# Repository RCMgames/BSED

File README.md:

# Byte Sized Encoder Decoder

Reads 8 quadrature encoders and communicates over I2C.

https://github.com/RCMgames/BSED

* Reads 8 quadrature encoders
* 1.0x0.85 inches, 25.4x21.59 millimeters
* I2C (Qwiic Compatible)
* powered by an ATmega328PB
* hand solderable surface mount components

### links 
(this repository contains an Arduino library, firmware for the board, and hardware for the board)
* [Documentation for Library](https://rcmgames.github.io/BSED/class_byte_sized_encoder_decoder.html)
* [Hardware](https://github.com/RCMgames/BSED/tree/main/extras/hardware)
  * If you buy PCBs from PCBWay through this link PCBWay generously gives me a 10% commission without costing you anything
    * https://www.pcbway.com/project/shareproject/ByteSizedEncoderDecoder_v1_1_a5a4bd50.html
* [Firmware](https://github.com/RCMgames/BSED/tree/main/extras/firmware)

### testing
Approximately 15000 encoder counts per second can be read from each encoder, but do your own testing before trusting this software.

See, and contribute to, this discussion on testing results: https://github.com/RCMgames/BSED/discussions/6

I've been working on [hardware and software for small wifi controlled robots](https://github.com/rcmgames) since 2020.

As I have designed increasingly small [circuit boards](https://github.com/rcmgames) for controlling servos and motors on robots, I started looking for a way to connect lots of quadrature encoders as inputs to a microcontroller. I was unable to find any existing Qwiic-compatible encoder reading boards that can handle multiple high-speed quadrature inputs. This board can help you control 8 motors with encoder feedback for precise control.

This version of firmware and library are compatible with version 1 of the hardware.

## Acknowledgements
* I would like to thank [PCBWay](https://www.pcbway.com/) for sponsoring prototyping runs of this project. PCBWay produces very nice boards, supports open source hardware, and gave me great support as I worked on this project. Special thanks to Liam!

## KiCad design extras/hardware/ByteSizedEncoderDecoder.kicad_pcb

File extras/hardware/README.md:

Here are the KiCAD and Gerber files for creating the circuit boards this firmware is designed to run on.

You could theoretically run it on a bare ATmega328 chip or another board, but the code is specialized for this board and uses hard-coded pin numbers.

### Bill Of Materials

* 1x assembled PCB
   * buy assembled PCBs from PCBWay with all the surface mount soldering done for you
      * https://www.pcbway.com/project/shareproject/ByteSizedEncoderDecoder_v1_1_a5a4bd50.html
   * or do your own surface mount soldering:
      * circuit board:
         * If you buy PCBs from PCBWay through this link PCBWay generously gives me a 10% commission without costing you anything
            * https://www.pcbway.com/project/shareproject/ByteSizedEncoderDecoder_v1_1_a5a4bd50.html
            * If you buy PCBs with another method (send ./PCB Production/gerbers-ByteSizedEncoderDecoder-v1.1.zip file) here's some info you might need: min track/spacing=6/6mil, min hole size=0.3mm
      * 2x JST SH https://www.digikey.com/en/products/detail/jst-sales-america-inc/SM04B-SRSS-TB/926710
      * 1x ATmega328PB TQFP https://www.digikey.com/en/products/detail/microchip-technology/ATMEGA328PB-AU/5638812
* 4x 1x08 0.1" female header pins

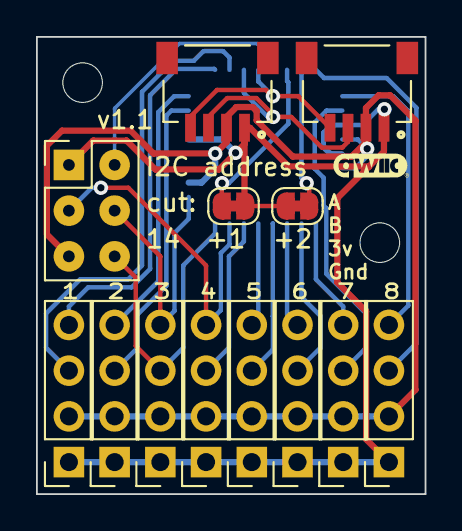
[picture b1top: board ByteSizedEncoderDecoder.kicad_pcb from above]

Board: 2 copper layers, 21.6 x 25.4 mm, 14 parts (1 on the bottom side), 23 nets.

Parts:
J1, J2: SM04B-SRSS-TB; JST_SM04B-SRSS-TB_LF__SN_
J3, J4, J5, J6, J7, J8, J9, J10: 1x4 female header pins 0.1"; PinSocket_1x04_P2.54mm_Vertical
J11: ICSP pads (for interfacing with pogo pins); PinHeader_2x03_P2.54mm_Vertical
NT1, NT2: NetTie_2; SolderJumper-2_P1.3mm_Bridged_RoundedPad1.0x1.5mm
U1: ATMEGA328PB, 32-TQFP; TQFP32_32A_MCH

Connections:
1a: J3.4, U1.25 (PC2(ADC2/PCINT10))
1b: J3.3, U1.26 (PC3(ADC3/PCINT11))
2a: J4.4, U1.24 (PC1(ADC1/PCINT9))
2b: J4.3, U1.23 (PC0(ADC0/PCINT8))
3a: J5.4, J11.4, U1.17 (PB5(SCK/PCINT5))
3b: J5.3, J11.6, U1.16 (PB4(PCINT4/MISO))
4a: J6.4, J11.3, U1.15 (PB3(PCINT3/OC2A/MOSI))
4b: J6.3, U1.14 (PB2(PCINT2/*SS/OC1B))
5a: J7.4, U1.13 (PB1(PCINT1/OC1A))
5b: J7.3, U1.12 (PB0(PCINT0/CLKO/ICP1))
6a: J8.4, U1.11 (PD7(PCINT23/AIN1))
6b: J8.3, U1.10 (PD6(PCINT22/OC0A/AIN0))
7a: J9.4, U1.9 (PD5(PCINT21/OC0B/T1))
7b: J9.3, U1.2 (PD4(PCINT20/XCK/T0))
8a: J10.4, U1.1 (PD3(PCINT19/OC2B/INT1))
8b: J10.3, U1.32 (PD2(INT0/PCINT18))
+3.3V: J1.2, J2.2, J3.2, J4.2, J5.2, J6.2, J7.2, J8.2, J9.2, J10.2, J11.5, U1.4 (VCC), U1.6 (VCC), U1.18 (AVCC)
GND: J1.1, J2.1, J3.1, J4.1, J5.1, J6.1, J7.1, J8.1, J9.1, J10.1, J11.1, NT1.2, NT2.2, U1.3 (GND), U1.5 (GND), U1.21 (GND)
unnamed: J11.2, U1.29 (PC6(*RESET/PCINT14))
unnamed: NT2.1, U1.30 (PD0(RXD/PCINT16))
unnamed: NT1.1, U1.31 (PD1(TXD/PCINT17))
scl: J1.4, J2.4, U1.28 (PC5(ADC5/SCL/PCINT13))
sda: J1.3, J2.3, U1.27 (PC4(ADC4/SDA/PCINT12))

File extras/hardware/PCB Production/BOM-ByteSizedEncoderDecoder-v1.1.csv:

"Reference","Value","Footprint","Datasheet","MPN","digikey link","Qty"
"J1, J2","SM04B-SRSS-TB","parts:JST_SM04B-SRSS-TB_LF__SN_","","SM04B-SRSS-TB","455-SM04B-SRSS-TBCT-ND","2"
"J3-J10","1x4 female header pins 0.1""","Connector_PinSocket_2.54mm:PinSocket_1x04_P2.54mm_Vertical","","do not place or purchase for PCB assembly","do not place or purchase for PCB assembly","8"
"J11","ICSP pads (for interfacing with pogo pins)","Connector_PinHeader_2.54mm:PinHeader_2x03_P2.54mm_Vertical","","DNP","n/a","1"
"NT1, NT2","NetTie_2","Jumper:SolderJumper-2_P1.3mm_Bridged_RoundedPad1.0x1.5mm","n/a","DNP","n/a","2"
"U1","ATMEGA328PB, 32-TQFP","parts:TQFP32_32A_MCH","https://ww1.microchip.com/downloads/en/DeviceDoc/40001907A.pdf","ATMEGA328PB-AU","ATMEGA328PB-AU-ND","1"

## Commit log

2024-04-29 Update LICENSE
2024-04-29 hardware
2024-04-29 v1.0
2024-04-30 add cad renders
2024-04-30 library in progress
2024-04-30 deploy: 8dd29d336e77dd8c4daba4778646e2d6889b8209
2024-04-30 update encoder-decoder
2024-04-30 deploy: 046cac742c8d4baad0db3d08612773206f1ff25a
2024-04-30 reorganize folder structure
2024-04-30 deploy: 2d5b23bad0e188f643c6baa7bf9b12540b59f16d
2024-04-30 deploy: 31a050b9553977e2c86f72bc61df8bde66f740fb
2024-04-30 deploy: 13ed9f9aa46e3a3bda3e58f608fc88605411b876
2024-04-30 deploy: ab928fcbb1b86652a8794f63fa460a9a4513bed8
2024-04-30 deploy: 84afdc5e6e0a747d372bb20c3929f94d8365258d
2024-04-30 deploy: c303ee2e10e87f0bf2600fd7d9f0ddd85b5686de
2024-04-30 deploy: 153a3cc4830325937b0cc74e23a72a057c9026b1
2024-04-30 deploy: 42606e44eb93d30457489d31a3c7e9c2847c78af
2024-04-30 update example
2024-04-30 deploy: 774eb56ce349130d670638287d715e6ee888093a
2024-05-07 update gitignore
2024-05-07 update platformio.ini for firmware
2024-05-07 update arduino-lint
2024-05-08 test board
2024-05-08 deploy: 01b0c1f6023ae4e33c418e61880ff35eee13345d
2024-05-08 v1.1.0
2024-05-08 deploy: 67b996aa6f6a97faa05906b41a075e949c9c572b
2024-05-08 deploy: 640480c00412bc1337e3585a3e5f8b7cb53df0ff
2024-05-08 deploy: bb7244fbd284bbc7ad47a52dc0187f68b3568ba5
2024-05-08 deploy: 7e8085068bbd8b13057818f64964c218992e2e56
2024-05-08 fix link
2024-05-08 deploy: a458f96f286acd965f08fd8f49f5cec25bdb48b6
2024-05-08 deploy: 14ca5f5b52133903bf38a4784cc1f2b9747e2a85
2024-05-08 bump version
2024-05-08 deploy: 7bbd7cdb57e76c38670929d11da173ca2910a05f
2024-05-09 deploy: 048ef7c90d99dd8eff31623957bd2c3ebbe873d6
2024-05-09 deploy: 2a934b6649cc7168c64c7b67ec340560d57a6b10
2024-05-09 deploy: a3604b6aac7eaefb1e5f3bccac8204a016fce239
2024-05-12 optimize
2024-05-12 deploy: fb2d7902788e27ff18d9947b4ad8f748b39b0092
2024-05-13 deploy: 2f7468403c3bd925679ba39fb191736a61d81592
2024-05-29 deploy: 74f35abdbd318b8f78ffbb224679e4cb3ca4ebe4
2024-05-29 deploy: 8e37769f0586e88a46bd28d0efe4ec72a4f9f8ab
2024-05-29 deploy: e4b2774a8f3d07a7a845fc5fdbfd15aabe313e3b
2024-06-01 v2 (velocity calculation and optimized communication)
2024-06-01 deploy: b679f1d842b0066368077c2ab96f58af3580ca96
2024-06-02 deploy: 839b353914f8db70047c15bcf3d98124fcc2ec9c
2024-06-02 deploy: 6aa68f8370d5924ac56f0b2442546248bb651869
2024-06-02 deploy: a9c9a5638a12d59224e219c59e79c5c87696c715
2024-06-02 add isvelnew
2024-06-02 deploy: 39d7633fdcdb4f595f88632ee2d85b5fb419ff88
2024-06-02 fix name conflict
2024-06-02 deploy: 23cef1622864e8e702abd88f5eae862d893afc08
2024-06-02 v2.1.2
2024-06-02 reset velocity when resetting position
2024-06-02 deploy: e5274b7ba16d88198c7ac8ed3aa3f12359599ac6
2024-06-02 v2.2.2
2024-06-02 deploy: e7d1fd530014e1fb585998c692609bd75ac072ad
2024-06-02 v2.3.3 bugfix for velocity calcs
2024-06-02 deploy: 5524da0fa868431ab668fc4fe1ad868691b30756
2024-06-04 fix bug in resetting variables
2024-06-04 deploy: a5c6d4dabe00a9de1f0777e7489a0b272e121e95
2024-06-05 add photos
2024-06-05 deploy: 22a19f413bf37448738e6ac1b0feb5361a8d2985
2025-03-20 deploy: fb91fdadd0e6dffe0a2f97e4015170253bf47a3a
2025-03-20 deploy: 192fa1e04a67a57baf54d26c0be9b26a3bd51981
2025-03-20 update date in license
